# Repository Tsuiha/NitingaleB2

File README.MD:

# Nitingale B2

「Nitingale B2」は、ゲーミングデバイスとして製作された左手デバイス／右手デバイスで、メカニカルスイッチを使用した自作キーボードです。

---

## 特徴

- **キー配列**  
  [Willow配列](https://coal.hatenablog.com/entry/2020/12/04/231923) や[Project mammoth](https://github.com/illness072/project-mammoth) からインスピレーションを受けてデザインされたキー配列で、無理のない指の可動域による運指をコンセプトとしています。  
  キースイッチ30個 + レバースイッチ1個の構成で、33のキー入力が可能です。

- **用途**  
  ゲーミングやアプリケーション操作を想定しており、多目的な用途に使用できるデバイスです。  
  左手用に加え、右手用もラインナップしています。

- **対応キースイッチ**  
  「Cherry MX」または「KS-33B Gateron Low Profile 3.0」に互換性のあるスイッチが使用できます。  
  キースイッチはMX用ホットスワップソケットにてPCBに接続します。

- **サイドスイッチ**  
  背面に3方向（左、右、押し込み）のレバースイッチを実装しています。  
  プロファイル切り替えやワンタッチで行いたい操作を割り振ることができます。

- **チルト／テントアングル**  
  専用ケースはチルト角6度、テント角3度の傾斜が設けられています。

---

## 仕様

| 項目 | 内容 |
|------|------|
| 接続 | USB Type-C（有線） |
| 入力数 | キースイッチ30入力／レバースイッチ3入力 |
| ファームウェア | QMK Firmware, [Nitingale B2 codes](https://github.com/Tsuiha/vial-qmk/tree/vial/keyboards/0_tsuiha/nitingale_b2)  |
| 設定ソフト | Vial |

---

## 構成

`Plate` - `PCB` - `Case` の3パーツ構成で、プレートマウント方式です。  
PCBはキースイッチを介してプレートに固定され、プレートはスタンドオフスペーサを介してケースに固定されます。

---

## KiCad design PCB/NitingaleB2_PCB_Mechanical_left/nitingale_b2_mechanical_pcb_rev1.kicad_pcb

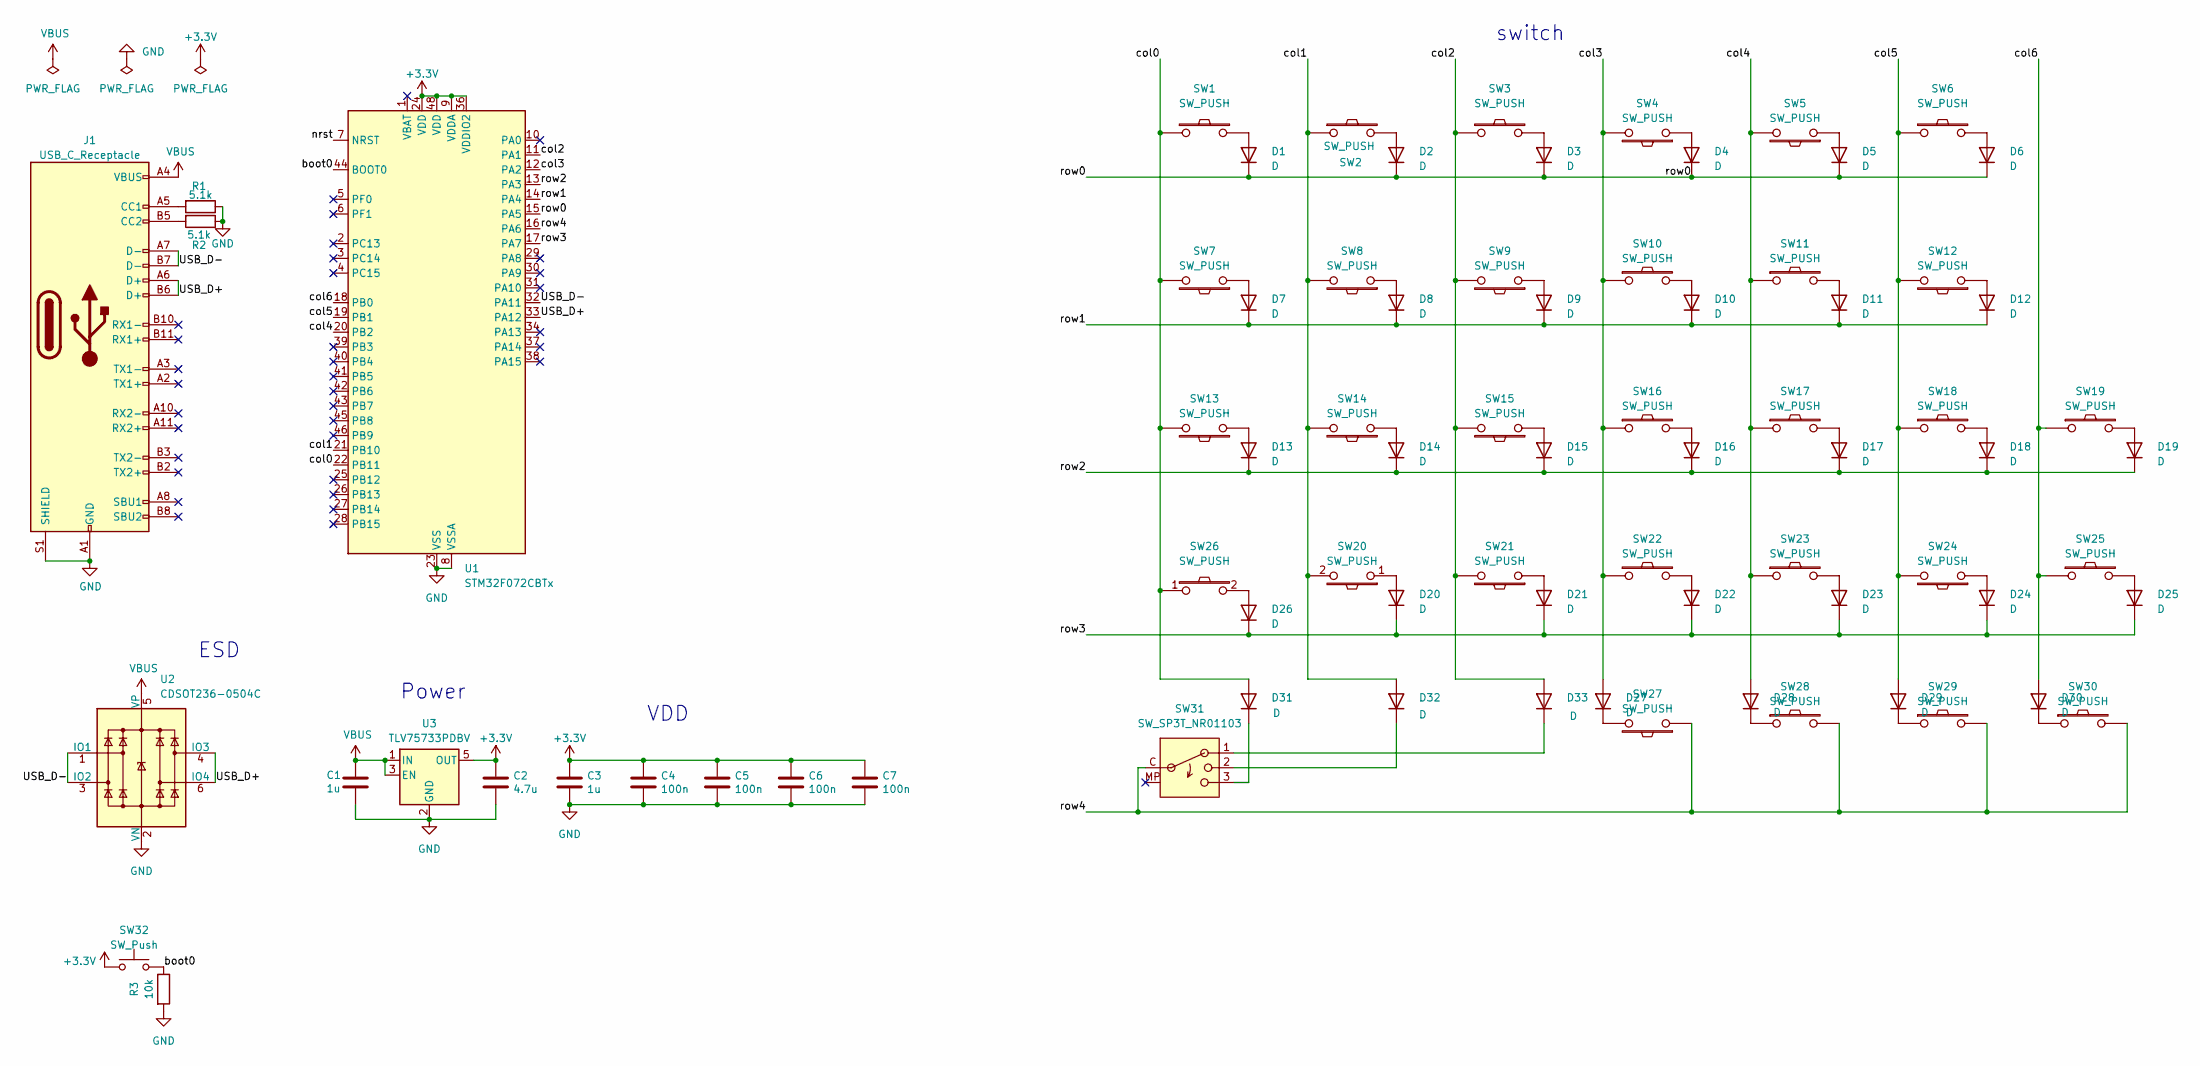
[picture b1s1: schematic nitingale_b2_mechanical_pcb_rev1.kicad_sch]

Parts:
C1, C3: 1u; C_0603_1608Metric
C2: 4.7u; C_0603_1608Metric
C4, C5, C6, C7: 100n; C_0603_1608Metric
D1, D2, D3, D4, D5, D6, D7, D8, D9, D10, D11, D12, D13, D14, D15, D16, D17, D18, D19, D20, D21, D22, D23, D24, D25, D26, D27, D28, D29, D30, D31, D32, D33: D; Diode_SMD_noname
J1: USB_C_Receptacle; USB_C_Receptacle_HRO_TYPE-C-31-M-12
R1, R2: 5.1k; C_0603_1608Metric
R3: 10k; C_0603_1608Metric
SW1, SW2, SW3, SW4, SW5, SW6, SW8, SW9, SW10, SW11, SW12, SW14, SW15, SW16, SW17, SW18, SW19, SW21, SW22, SW23, SW24, SW25, SW27, SW28, SW29, SW30: SW_PUSH; MX_GLPV3_1U
SW7: SW_PUSH; MX_GLPV3_1.5U
SW13, SW20: SW_PUSH; MX_GLPV3_1.75U
SW26: SW_PUSH; MX_GLPV3_1.25U
SW31: SW_SP3T_NR01103; TMHU27
SW32: SW_Push; SW_SPST_SKQG_WithStem
U1: STM32F072CBTx; LQFP-48_7x7mm_P0.5mm
U2: CDSOT236-0504C; sot-23-6-USBESD
U3: TLV75733PDBV; SOT-23-5

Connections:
+3.3V: C2.1, C3.1, C4.1, C5.1, C6.1, C7.1, SW32.1, U1.9 (VDDA), U1.24 (VDD), U1.36 (VDDIO2), U1.48 (VDD), U3.5 (OUT)
/USB_D+: J1.A6 (D+), J1.B6 (D+), U1.33 (PA12), U2.4 (IO3), U2.6 (IO4)
/USB_D-: J1.A7 (D-), J1.B7 (D-), U1.32 (PA11), U2.1 (IO1), U2.3 (IO2)
/boot0: R3.1, SW32.2, U1.44 (BOOT0)
/col0: D31.2 (A), SW1.1, SW7.2, SW13.2, SW26.1, U1.22 (PB11)
/col1: D32.2 (A), SW2.1, SW8.2, SW14.2, SW20.2, U1.21 (PB10)
/col2: D33.2 (A), SW3.1, SW9.2, SW15.2, SW21.2, U1.11 (PA1)
/col3: D27.2 (A), SW4.2, SW10.1, SW16.1, SW22.1, U1.12 (PA2)
/col4: D28.2 (A), SW5.2, SW11.1, SW17.1, SW23.1, U1.20 (PB2)
/col5: D29.2 (A), SW6.1, SW12.2, SW18.1, SW24.2, U1.19 (PB1)
/col6: D30.2 (A), SW19.1, SW25.1, U1.18 (PB0)
/nrst: U1.7 (NRST)
/row0: D1.1 (K), D2.1 (K), D3.1 (K), D4.1 (K), D5.1 (K), D6.1 (K), U1.15 (PA5)
/row1: D7.1 (K), D8.1 (K), D9.1 (K), D10.1 (K), D11.1 (K), D12.1 (K), U1.14 (PA4)
/row2: D13.1 (K), D14.1 (K), D15.1 (K), D16.1 (K), D17.1 (K), D18.1 (K), D19.1 (K), U1.13 (PA3)
/row3: D20.1 (K), D21.1 (K), D22.1 (K), D23.1 (K), D24.1 (K), D25.1 (K), D26.1 (K), U1.17 (PA7)
/row4: SW27.1, SW28.2, SW29.2, SW30.2, SW31.C (Common), U1.16 (PA6)
GND: C1.2, C2.2, C3.2, C4.2, C5.2, C6.2, C7.2, J1.A1 (GND), J1.A12 (GND), J1.B1 (GND), J1.B12 (GND), J1.S1 (SHIELD), R1.1, R2.1, R3.2, U1.8 (VSSA), U1.23 (VSS), U1.35 (VSS), U1.47 (VSS), U2.2 (VN), U3.2 (GND)
unnamed: D1.2 (A), SW1.2
unnamed: D2.2 (A), SW2.2
unnamed: D3.2 (A), SW3.2
unnamed: D4.2 (A), SW4.1
unnamed: D5.2 (A), SW5.1
unnamed: D6.2 (A), SW6.2
unnamed: D7.2 (A), SW7.1
unnamed: D8.2 (A), SW8.1
unnamed: D9.2 (A), SW9.1
unnamed: D10.2 (A), SW10.2
unnamed: D11.2 (A), SW11.2
unnamed: D12.2 (A), SW12.1
unnamed: D13.2 (A), SW13.1
unnamed: D14.2 (A), SW14.1
unnamed: D15.2 (A), SW15.1
unnamed: D16.2 (A), SW16.2
unnamed: D17.2 (A), SW17.2
unnamed: D18.2 (A), SW18.2
unnamed: D19.2 (A), SW19.2
unnamed: D20.2 (A), SW20.1
unnamed: D21.2 (A), SW21.1
unnamed: D22.2 (A), SW22.2
unnamed: D23.2 (A), SW23.2
unnamed: D24.2 (A), SW24.1
unnamed: D25.2 (A), SW25.2
unnamed: D26.2 (A), SW26.2
unnamed: D27.1 (K), SW27.2
unnamed: D28.1 (K), SW28.1
unnamed: D29.1 (K), SW29.1
unnamed: D30.1 (K), SW30.1
unnamed: D31.1 (K), SW31.3
unnamed: D32.1 (K), SW31.2
unnamed: D33.1 (K), SW31.1
unnamed: J1.A5 (CC1), R1.2
unnamed: J1.B5 (CC2), R2.2
VBUS: C1.1, J1.A4 (VBUS), J1.A9 (VBUS), J1.B4 (VBUS), J1.B9 (VBUS), U2.5 (VP), U3.1 (IN), U3.3 (EN)

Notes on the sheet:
Power
switch
ESD
VDD

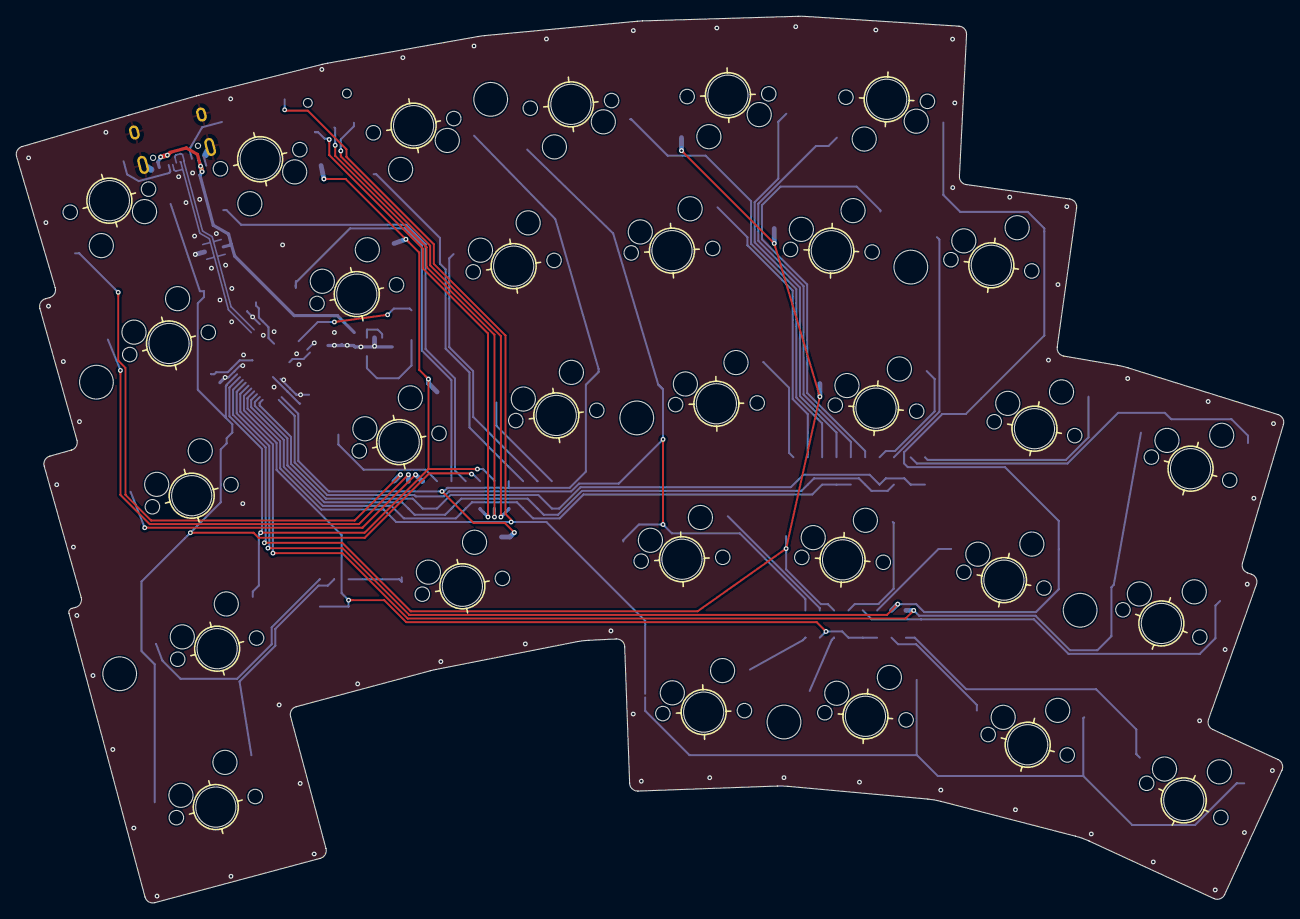
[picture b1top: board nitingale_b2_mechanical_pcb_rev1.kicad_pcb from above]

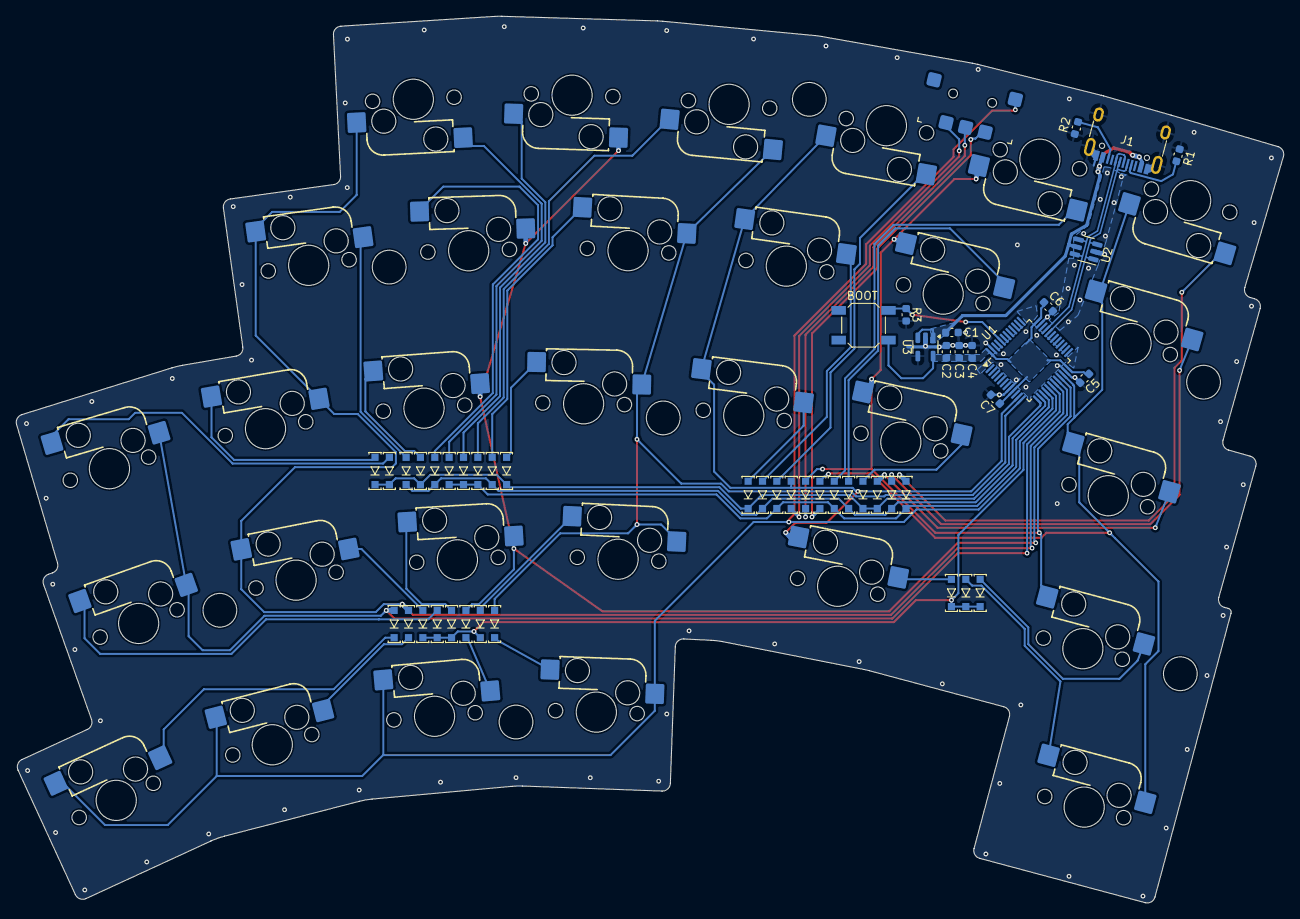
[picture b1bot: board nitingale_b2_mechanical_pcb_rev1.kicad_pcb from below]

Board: 2 copper layers, 157.7 x 110.3 mm, 86 parts (16 on the bottom side), 53 nets.

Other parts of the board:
Ref**: Val**; hole_4mm
Ref**#2, Ref**#3, Ref**#4, Ref**#5, Ref**#6, Ref**#7: Val**; hole_4mm

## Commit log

2025-11-01 Update README with Nitingale B2 details
2025-11-01 Update readme with PLT standoff spacer details
    Added notes about the PLT standoff spacer inclusion.
